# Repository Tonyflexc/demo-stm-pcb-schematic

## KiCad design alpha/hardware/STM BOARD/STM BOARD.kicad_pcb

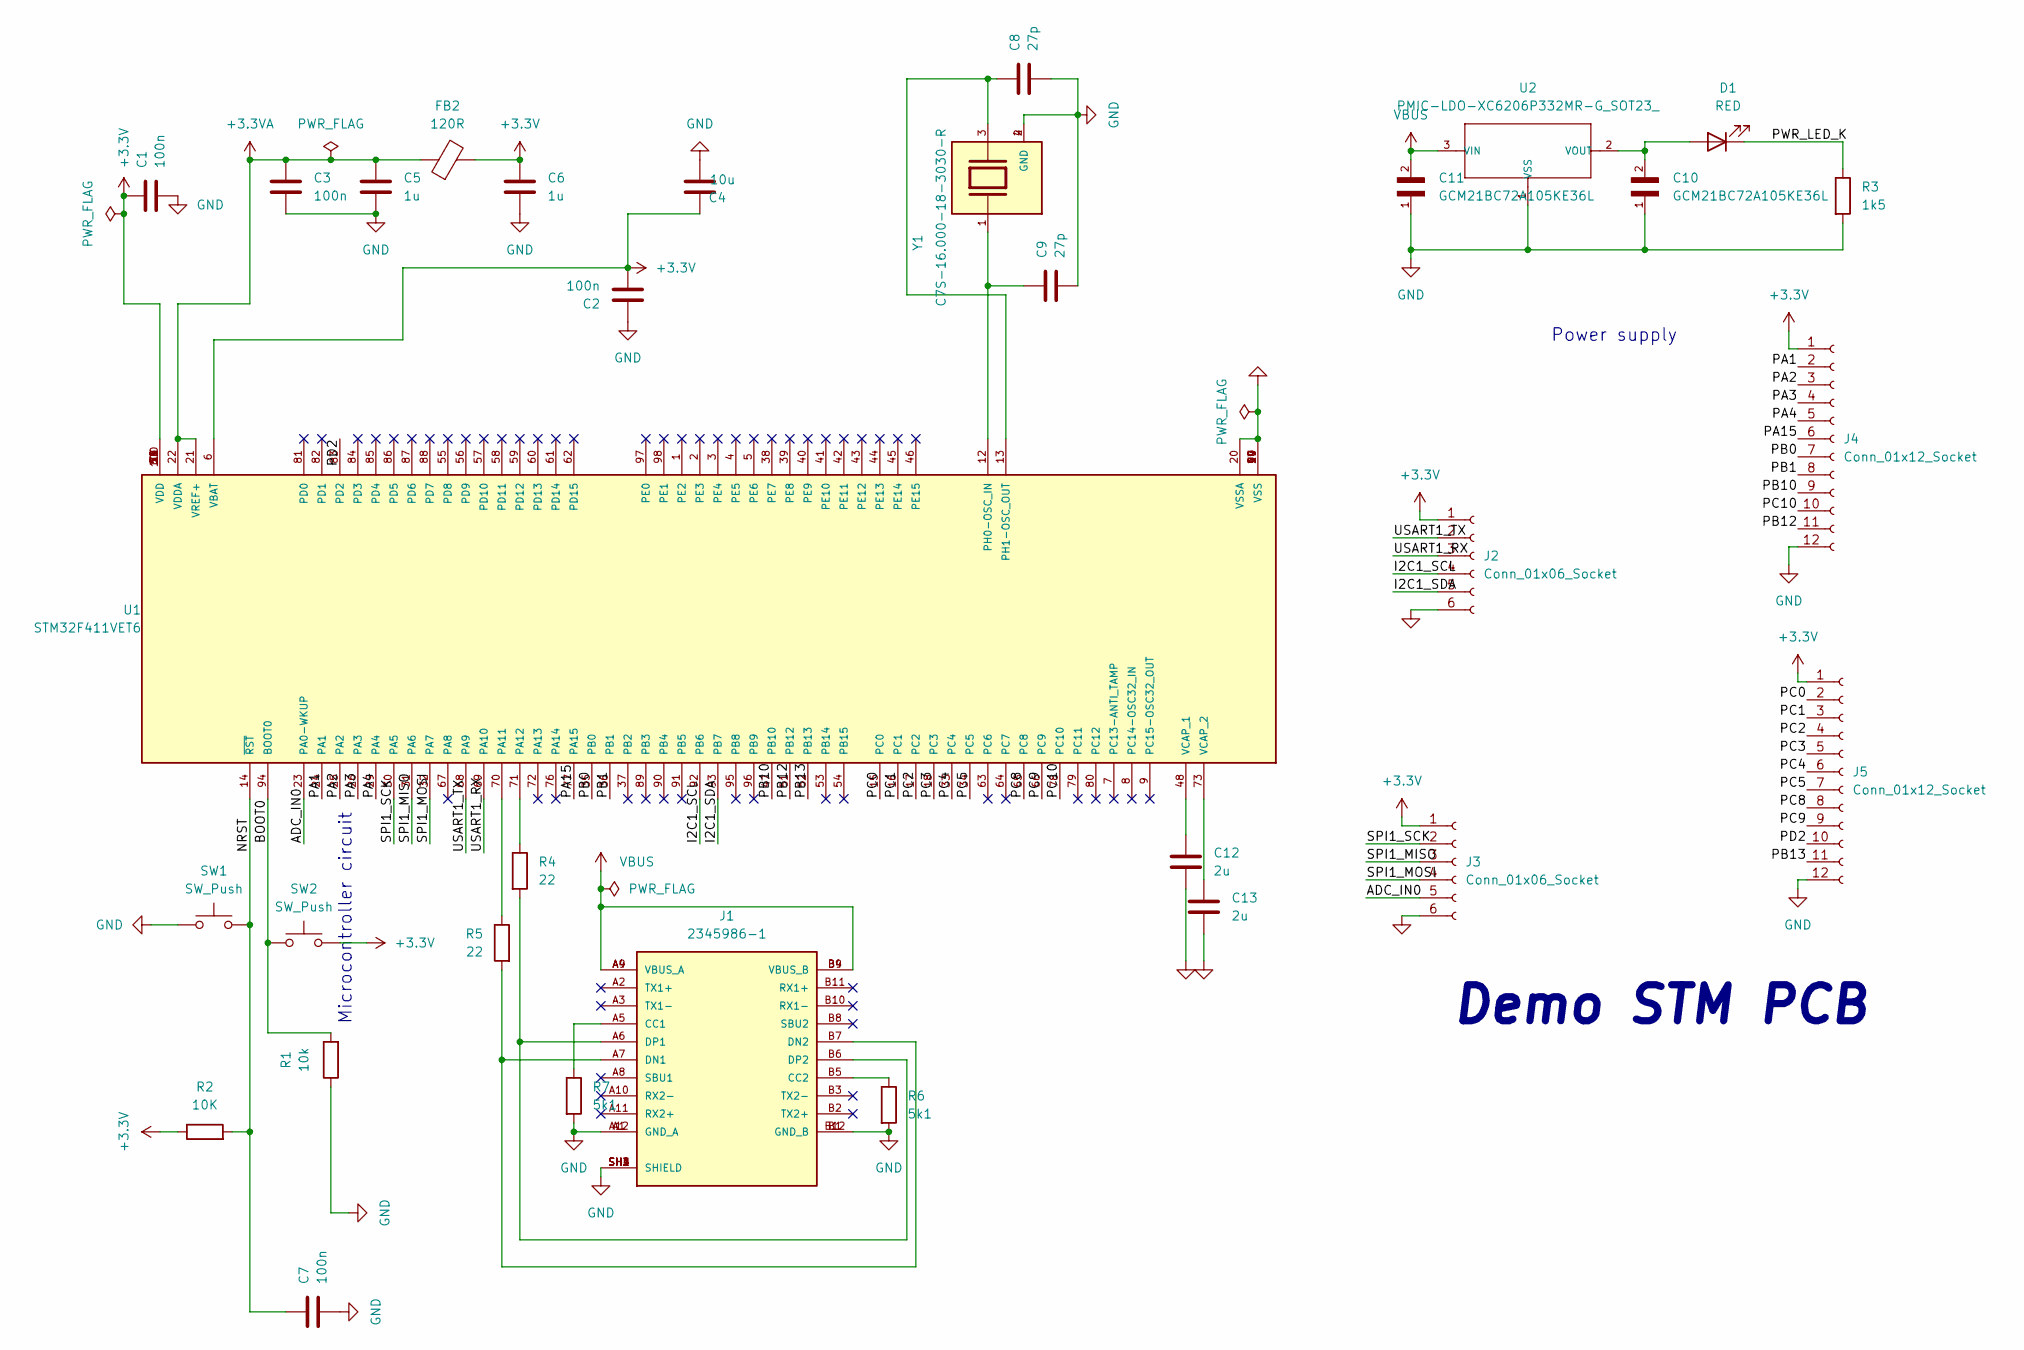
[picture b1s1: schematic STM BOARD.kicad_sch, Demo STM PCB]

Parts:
C1, C2, C3, C7: 100n; C_0603_1608Metric
C4: 10u; C_0805_2012Metric
C5, C6: 1u; C_0603_1608Metric
C8, C9: 27p; C_0402_1005Metric
C10, C11: GCM21BC72A105KE36L; CAPC2012X145N
C12, C13: 2u; C_0603_1608Metric
D1: RED; LED_0603_1608Metric
FB2: 120R; L_0603_1608Metric
J1: 2345986-1; TE_2345986-1; PARTREV C
J2, J3: Conn_01x06_Socket; PinSocket_1x06_P2.54mm_Vertical
J4, J5: Conn_01x12_Socket; PinSocket_1x12_P2.54mm_Vertical
R1: 10k; R_0603_1608Metric
R2: 10K; R_0603_1608Metric
R3: 1k5; R_0603_1608Metric
R4, R5: 22; R_0603_1608Metric
R6, R7: 5k1; R_0603_1608Metric
SW1, SW2: SW_Push; SW_PUSH_6mm_H9.5mm
U1: STM32F411VET6; QFP50P1600X1600X160-100N; PARTREV 7
U2: PMIC-LDO-XC6206P332MR-G_SOT23_; SOT-23; MPN XC6206P332MR-G
Y1: C7S-16.000-18-3030-R; XTAL_C7S-16.000-18-3030-R; PARTREV N/A

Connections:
+3.3V: C1.2, C2.2, C4.1, C6.2, FB2.2, J2.1, J3.1, J4.1, J5.1, R2.1, SW2.2, U1.6 (VBAT), U1.11 (VDD), U1.19 (VDD), U1.28 (VDD), U1.50 (VDD), U1.75 (VDD), U1.100 (VDD)
+3.3VA: C3.2, C5.2, FB2.1, U1.21 (VREF+), U1.22 (VDDA)
/ADC_IN0: J3.5, U1.23 (PA0-WKUP)
/BOOT0: R1.2, SW2.1, U1.94 (BOOT0)
/I2C1_SCL: J2.4, U1.92 (PB6)
/I2C1_SDA: J2.5, U1.93 (PB7)
/NRST: C7.2, R2.2, SW1.2, U1.14 (~RST)
/PA1: J4.2, U1.24 (PA1)
/PA2: J4.3, U1.25 (PA2)
/PA3: J4.4, U1.26 (PA3)
/PA4: J4.5, U1.29 (PA4)
/PA15: J4.6, U1.77 (PA15)
/PB0: J4.7, U1.35 (PB0)
/PB1: J4.8, U1.36 (PB1)
/PB10: J4.9, U1.47 (PB10)
/PB12: J4.11, U1.51 (PB12)
/PB13: J5.11, U1.52 (PB13)
/PC0: J5.2, U1.15 (PC0)
/PC1: J5.3, U1.16 (PC1)
/PC2: J5.4, U1.17 (PC2)
/PC3: J5.5, U1.18 (PC3)
/PC4: J5.6, U1.33 (PC4)
/PC5: J5.7, U1.34 (PC5)
/PC8: J5.8, U1.65 (PC8)
/PC9: J5.9, U1.66 (PC9)
/PC10: J4.10, U1.78 (PC10)
/PD2: J5.10, U1.83 (PD2)
/PWR_LED_K: D1.1 (K), R3.1
/SPI1_MISO: J3.3, U1.31 (PA6)
/SPI1_MOSI: J3.4, U1.32 (PA7)
/SPI1_SCK: J3.2, U1.30 (PA5)
/USART1_RX: J2.3, U1.69 (PA10)
/USART1_TX: J2.2, U1.68 (PA9)
/USB_DN_CONN: J1.A7 (DN1), J1.B7 (DN2), R5.2; also elsewhere on the board
/USB_DP_CONN: J1.A6 (DP1), J1.B6 (DP2), R4.2; also elsewhere on the board
GND: C1.1, C2.1, C3.1, C4.2, C5.1, C6.1, C7.1, C8.2, C9.2, C10.1, C11.1, C12.2, C13.2, J1.A1 (GND_A), J1.A12 (GND_A), J1.B1 (GND_B), J1.B12 (GND_B), J1.SH1 (SHIELD), J1.SH2 (SHIELD), J1.SH3 (SHIELD), J1.SH4 (SHIELD), J2.6, J3.6, J4.12, J5.12, R1.1, R3.2, R6.2, R7.2, SW1.1, U1.10 (VSS), U1.20 (VSSA), U1.27 (VSS), U1.49 (VSS), U1.74 (VSS), U1.99 (VSS), U2.1 (VSS), Y1.2 (GND), Y1.4 (GND); also elsewhere on the board
unnamed: C10.2, D1.2 (A), U2.2 (VOUT)
unnamed: J1.A5 (CC1), R7.1
unnamed: J1.B5 (CC2), R6.1
unnamed: R5.1, U1.70 (PA11)
unnamed: R4.1, U1.71 (PA12)
unnamed: C9.1, U1.12 (PH0-OSC_IN), Y1.1
unnamed: C8.1, U1.13 (PH1-OSC_OUT), Y1.3
unnamed: C12.1, U1.48 (VCAP_1)
unnamed: C13.1, U1.73 (VCAP_2)
VBUS: C11.2, J1.A4 (VBUS_A), J1.A9 (VBUS_A), J1.B4 (VBUS_B), J1.B9 (VBUS_B), U2.3 (VIN)

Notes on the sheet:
Power supply
Microcontroller circuit
Demo STM PCB

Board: 4 copper layers, 33 parts (0 on the bottom side), 46 nets, no tracks yet.

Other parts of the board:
D2: ESDA5V3L; SOT-23-3

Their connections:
/USB_DN_CONN: D2.2 (K); also elsewhere on the board
/USB_DP_CONN: D2.1 (K); also elsewhere on the board
GND: D2.3 (A); also elsewhere on the board
